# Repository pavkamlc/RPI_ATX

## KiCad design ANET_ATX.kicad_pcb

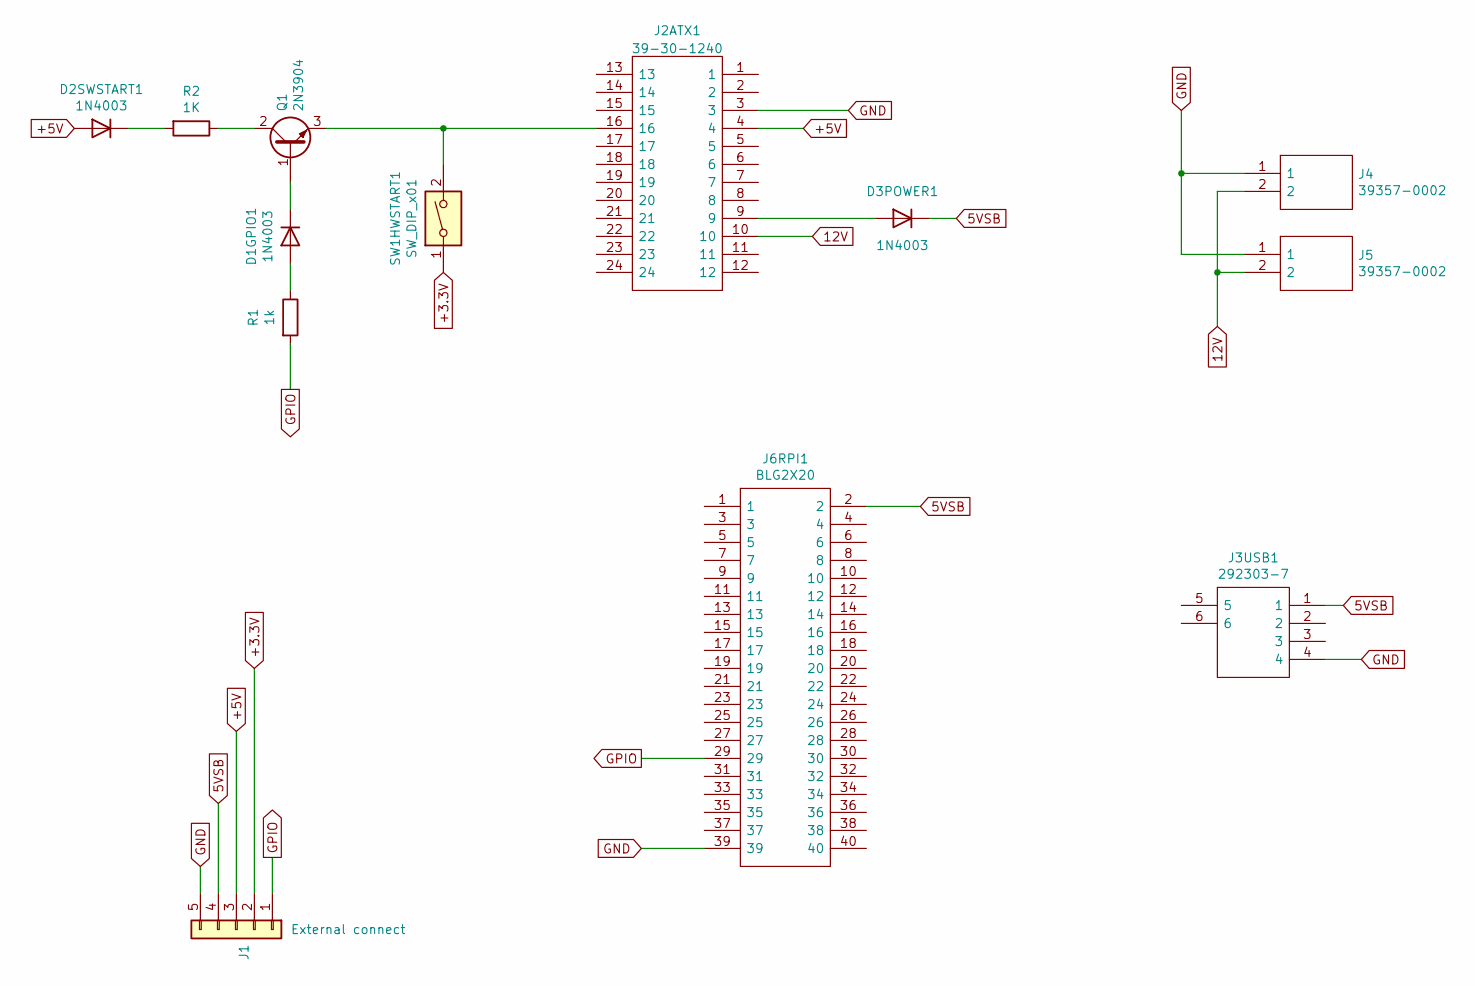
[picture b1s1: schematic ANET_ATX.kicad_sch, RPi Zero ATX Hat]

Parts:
D1GPIO1, D2SWSTART1, D3POWER1: 1N4003; LED_D3.0mm
J1: External connect; PinHeader_1x05_P2.54mm_Vertical
J2ATX1: 39-30-1240; 39-30-124Y_012; Manufacturer_Part_Number 39-30-1240; Mouser Part Number 538-39-30-1240
J3USB1: 292303-7; A-USBSA; Manufacturer_Part_Number 292303-7; Mouser Part Number 571-292303-7
J4, J5: 39357-0002; 0398800302; Manufacturer_Part_Number 39357-0002; Mouser Part Number 538-39357-0002
J6RPI1: BLG2X20; RHDR40W64P254_2X20_5130X500X1375P; Manufacturer_Part_Number BLG2X20
Q1: 2N3904; TO-92_Inline
R1: 1k; R_Axial_DIN0207_L6.3mm_D2.5mm_P7.62mm_Horizontal
R2: 1K; R_Axial_DIN0207_L6.3mm_D2.5mm_P7.62mm_Horizontal
SW1HWSTART1: SW_DIP_x01; SW_DIP_SPSTx01_Slide_6.7x4.1mm_W7.62mm_P2.54mm_LowProfile

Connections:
5VSB: D3POWER1.1 (K), J1.4, J3USB1.1, J6RPI1.2
12V: J2ATX1.10, J4.2, J5.2
+3.3V: J1.2, SW1HWSTART1.1
+5V: D2SWSTART1.2 (A), J1.3, J2ATX1.4
GND: J1.5, J2ATX1.3, J3USB1.4, J4.1, J5.1, J6RPI1.39
GPIO: J1.1, J6RPI1.29, R1.2
unnamed: D1GPIO1.1 (K), Q1.1 (B)
unnamed: D1GPIO1.2 (A), R1.1
unnamed: D2SWSTART1.1 (K), R2.2
unnamed: D3POWER1.2 (A), J2ATX1.9
unnamed: J2ATX1.16, Q1.3 (E), SW1HWSTART1.2
unnamed: Q1.2 (C), R2.1

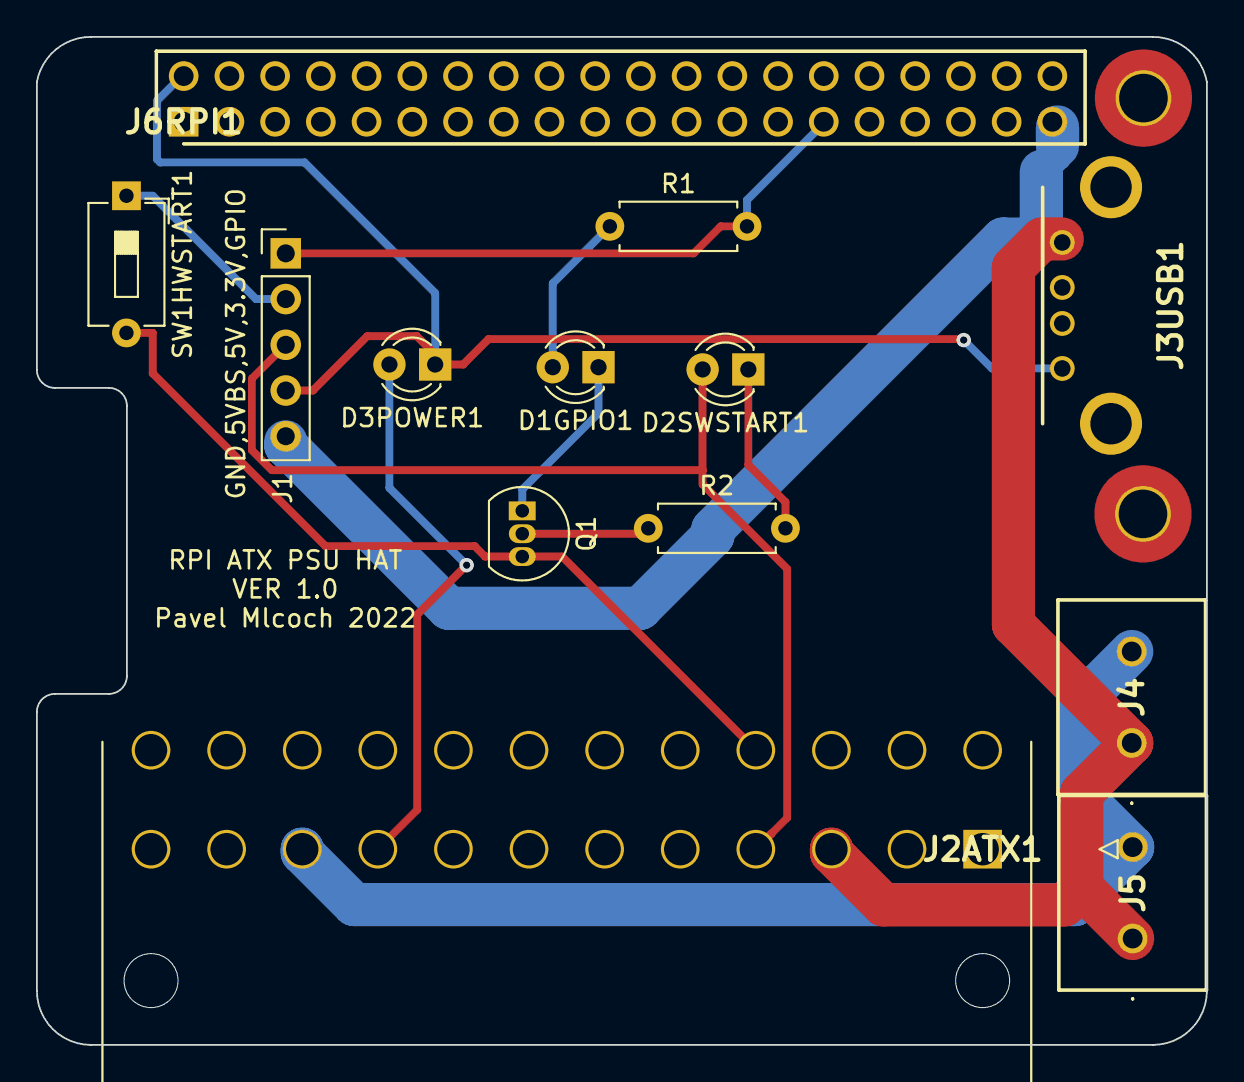
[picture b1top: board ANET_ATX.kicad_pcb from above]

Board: 2 copper layers, 65.0 x 56.0 mm, 15 parts (0 on the bottom side), 12 nets.

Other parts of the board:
H1: H1; MountingHole_2.7mm_M2.5_Pad_TopBottom
H3: H3; MountingHole_2.7mm_M2.5_Pad_TopBottom

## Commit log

2022-12-20 cleanup
2023-02-02 freshes
2023-02-20 replaced best parts
